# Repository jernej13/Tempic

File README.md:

# Tempic
Small 50mm x 50mm solar powered ESP32c6 based indoor/outdoor WiFi/Zigbee sensor node.

# Features
- Onboard ESP32 C6 mini with
    - WiFi 6 (2.4 GHz)
    - Zigbee 3
    - Bluetooth 5.3

- BME688
    - Temperature
    - Humidity
    - Pressure
    - CO2 
    
- BMV080 (for outdoor use)
    - P.M. 1.0
    - P.M. 2.5
    - P.M. 10

- Small 5x5cm solar panel
- Small 5x5cm LiPo battery

Goal is easy Home Assistant integration with unlimited battery life and cable-less deployment.
# Roadmap
- [x] Hardware 1.0
    - [x] Find suitable ICs
    - [x] Schematics 1.0
    - [x] Draw PCB 1.0
    - [x] Order prototype
    - [x] Assemble the PCB
    - [x] Test PCB
- [ ] Hardware 1.1
    - [ ] Fix current PCB mistakes
    - [ ] Order PCB
    - [ ] Assemble and test PCB
- [ ] Firmware
    - [x] Basic test and demo of sensors
    - [ ] Battery life optimization
    - [ ] Add Wifi
    - [ ] Setup connection to Home Assistant
    - [ ] Add Zigbee
    - [ ] (far) Add BLE peer to peer communication for bigger meshes
- [ ] Case
    - [ ] 3d design case
    - [ ] 3d print case  
- [ ] Home assistant
    - [ ] Figure out what is the best way to make it work (do not know if any custom plugins are necessary)
     
# Schematics
View [schematics](media/Schematics_1.0.pdf) in PDF format.

Developed in KiCad.

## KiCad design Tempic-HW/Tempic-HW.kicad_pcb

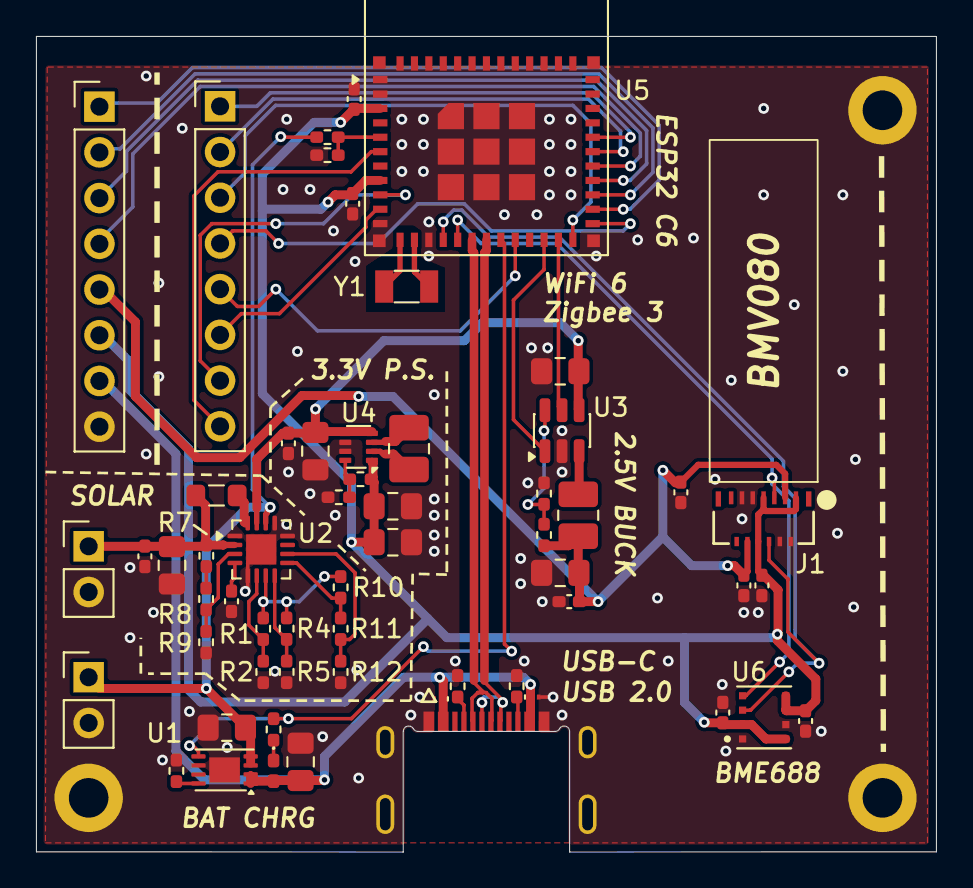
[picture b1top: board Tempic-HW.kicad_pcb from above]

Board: 2 copper layers, 50.0 x 45.3 mm, 58 parts (0 on the bottom side), 47 nets.

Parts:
BT1: LiPo; PinHeader_1x02_P2.54mm_Vertical
C1, C3, C5, C7: 4.7u; C_0805_2012Metric_Pad1.18x1.45mm_HandSolder
C2, C6, C12, C13, C14, C15, C16, C17, C18, C19: 100n; C_0402_1005Metric_Pad0.74x0.62mm_HandSolder
C4: 10n; C_0402_1005Metric_Pad0.74x0.62mm_HandSolder
C8, C9, C10, C11: 22u; C_0805_2012Metric_Pad1.18x1.45mm_HandSolder
D1: LED; LED_0402_1005Metric_Pad0.77x0.64mm_HandSolder
D2, D3: ESDZV5-1BV2; Nexperia_DSN0603-2_0.6x0.3mm_P0.4mm
J1: BMV080; CON_5035661302_MOL
J2, J3: Conn_01x08_Pin; PinHeader_1x08_P2.54mm_Vertical
L1: 22u; L_0805_2012Metric_Pad1.05x1.20mm_HandSolder
L2, L3: 1u; L_1008_2520Metric_Pad1.43x2.20mm_HandSolder
P1: 217175-0001; MOLEX_2169900001
R1, R4: 5.49M; R_0402_1005Metric_Pad0.72x0.64mm_HandSolder
R2, R5: 4.42M; R_0402_1005Metric_Pad0.72x0.64mm_HandSolder
R3: 470; R_0402_1005Metric_Pad0.72x0.64mm_HandSolder
R6: 2k; R_0402_1005Metric_Pad0.72x0.64mm_HandSolder
R7, R19, R20: 2.8M; R_0402_1005Metric_Pad0.72x0.64mm_HandSolder
R8: 10M; R_0402_1005Metric_Pad0.72x0.64mm_HandSolder
R9: 7.2M; R_0402_1005Metric_Pad0.72x0.64mm_HandSolder
R10: 316k; R_0402_1005Metric_Pad0.72x0.64mm_HandSolder
R11: 5.62M; R_0402_1005Metric_Pad0.72x0.64mm_HandSolder
R12: 4.02M; R_0402_1005Metric_Pad0.72x0.64mm_HandSolder
R13, R14: 5.1k; R_0402_1005Metric_Pad0.72x0.64mm_HandSolder
R15: 287k; R_0402_1005Metric_Pad0.72x0.64mm_HandSolder
R16, R18: 91k; R_0402_1005Metric_Pad0.72x0.64mm_HandSolder
R17: 511k; R_0402_1005Metric_Pad0.72x0.64mm_HandSolder
SC1: Solar_Cell; PinHeader_1x02_P2.54mm_Vertical
U1: MCP73831-2-MC; DFN-8-1EP_3x2mm_P0.5mm_EP1.7x1.4mm
U2: BQ25504; VQFN-16-1EP_3x3mm_P0.5mm_EP1.68x1.68mm
U3: TPS62A01PDDC; SOT-23-6
U4: TPS631000; SOT-583-8
U5: ESP32-C6-MINI-1
U6: BME688
Y1: 32.7680k; Crystal_SMD_3215-2Pin_3.2x1.5mm

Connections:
+2.5V: C10.1, C12.1, C15.1, C17.1, J1.3, J1.10, J3.5, L3.2, R15.1
+3.3V: C9.1, C11.1, C13.1, C14.1, C16.1, C18.1, C19.1, J1.1, J1.7, J1.8, J3.6, R17.1, U4.1 (VOUT), U5.3 (3V3), U5.8 (EN), U6.2 (CSB), U6.5 (SDO), U6.6 (V_{DDIO}), U6.8 (V_{DD})
+5V: C1.1, D1.2 (A), D2.1 (K), D3.1 (K), J3.7, P1.A4 (VBUS), P1.A9 (VBUS), U1.1 (V_{DD}), U1.2 (V_{DD})
/2.5V_EN: U3.1 (EN), U5.22 (IO8)
/2.5V_PG: U3.5 (PG), U5.23 (IO9)
/BAT: BT1.1 (+), C5.1, R19.1, U1.3 (V_{BAT}), U1.4 (V_{BAT}), U2.14 (VBAT)
/BAT_ADC: R19.2, R20.1, U5.5 (IO2)
/IO3: J2.8, U5.6 (IO3)
/IO4: J2.7, U5.9 (IO4)
/IO5: J2.6, U5.10 (IO5)
/IO15: J2.5, U5.20 (IO15)
/IO18: J2.3, U5.24 (IO18)
/IO19: J2.4, U5.25 (IO19)
/IO20: J3.1, U5.26 (IO20)
/IO21: J3.2, U5.27 (IO21)
/IO22: J3.3, U5.28 (IO22)
/IO23: J3.4, U5.29 (IO23)
/OK_HYST: R10.2, R11.1, U2.9 (OK_HYST)
/OK_PROG: R11.2, R12.1, U2.10 (OK_PROG)
/RXDO: J2.2, U5.30 (RXD0)
/SCL: J1.5, U5.16 (IO7), U6.4 (SCK)
/SDA: J1.6, U5.15 (IO6), U6.3 (SDI)
/STAT: R3.2, U1.5 (STAT), U5.19 (IO14)
/TXDO: J2.1, U5.31 (TXD0)
/USB_D+: P1.A6 (D+), P1.B6 (D+), U5.18 (IO13)
/USB_D-: P1.A7 (D-), P1.B7 (D-), U5.17 (IO12)
/VBAT_OV: R1.2, R2.1, U2.6 (VBAT_OV)
/VBAT_UV: R4.2, R5.1, U2.8 (VBAT_UV)
/VRDIV: R1.1, R4.1, R10.1, U2.7 (VRDIV)
GND: BT1.2 (-), C1.2, C2.2, C3.2, C4.2, C5.2, C6.2, C7.2, C8.2, C9.2, C10.2, C11.2, C12.2, C13.2, C14.2, C15.2, C16.2, C17.2, C18.2, C19.2, D2.2 (A), D3.2 (A), J1.2, J1.4, J1.9, J1.11, J3.8, P1.A1 (GND), P1.A12 (GND), P1.SH (SHIELD), R2.2, R5.2, R6.2, R9.2, R12.2, R13.2, R14.2, R16.2, R18.2, R20.2, SC1.2 (-), U1.6 (V_{SS}), U1.9 (V_{SS}), U2.1 (VSS), U2.5 (OT_PROG), U2.12 (AVSS), U2.13 (VSS), U2.17 (PAD), U3.2 (GND), U4.6 (MODE), U4.7 (GND), U5.1 (GND), U5.2 (GND), U5.11 (GND), U5.14 (GND), U5.36 (GND), U5.37 (GND), U5.38 (GND), U5.39 (GND), U5.40 (GND), U5.41 (GND), U5.42 (GND), U5.43 (GND), U5.44 (GND), U5.45 (GND), U5.46 (GND), U5.47 (GND), U5.48 (GND), U5.49 (GND), U5.50 (GND), U5.51 (GND), U5.52 (GND), U5.53 (GND), U6.1 (GND), U6.7 (GND)
unnamed: D1.1 (K), R3.1
unnamed: P1.A5 (CC1), R14.1
unnamed: P1.B5 (CC2), R13.1
unnamed: R7.2, R8.1
unnamed: C2.1, C3.1, L1.1, R7.1, SC1.1 (+), U2.2 (VIN_DC)
unnamed: R6.1, U1.8 (PROG)
unnamed: L1.2, U2.16 (LBST)
unnamed: R8.2, R9.1, U2.3 (VOC_SAMP)
unnamed: C4.1, U2.4 (VREF_SAMP)
unnamed: C6.1, C7.1, C8.1, U2.15 (VSTOR), U3.4 (VIN), U4.4 (VIN), U4.5 (EN)
unnamed: R15.2, R16.1, U3.6 (FB)
unnamed: L3.1, U3.3 (SW)
unnamed: R17.2, R18.1, U4.8 (FB)
unnamed: L2.1, U4.3 (LX1)
unnamed: L2.2, U4.2 (LX2)
unnamed: U5.12 (IO0), Y1.1
unnamed: U5.13 (IO1), Y1.2
